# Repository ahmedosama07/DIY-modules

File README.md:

# DIY-modules
 This is the repo where I try to recreate electronic modules at home.

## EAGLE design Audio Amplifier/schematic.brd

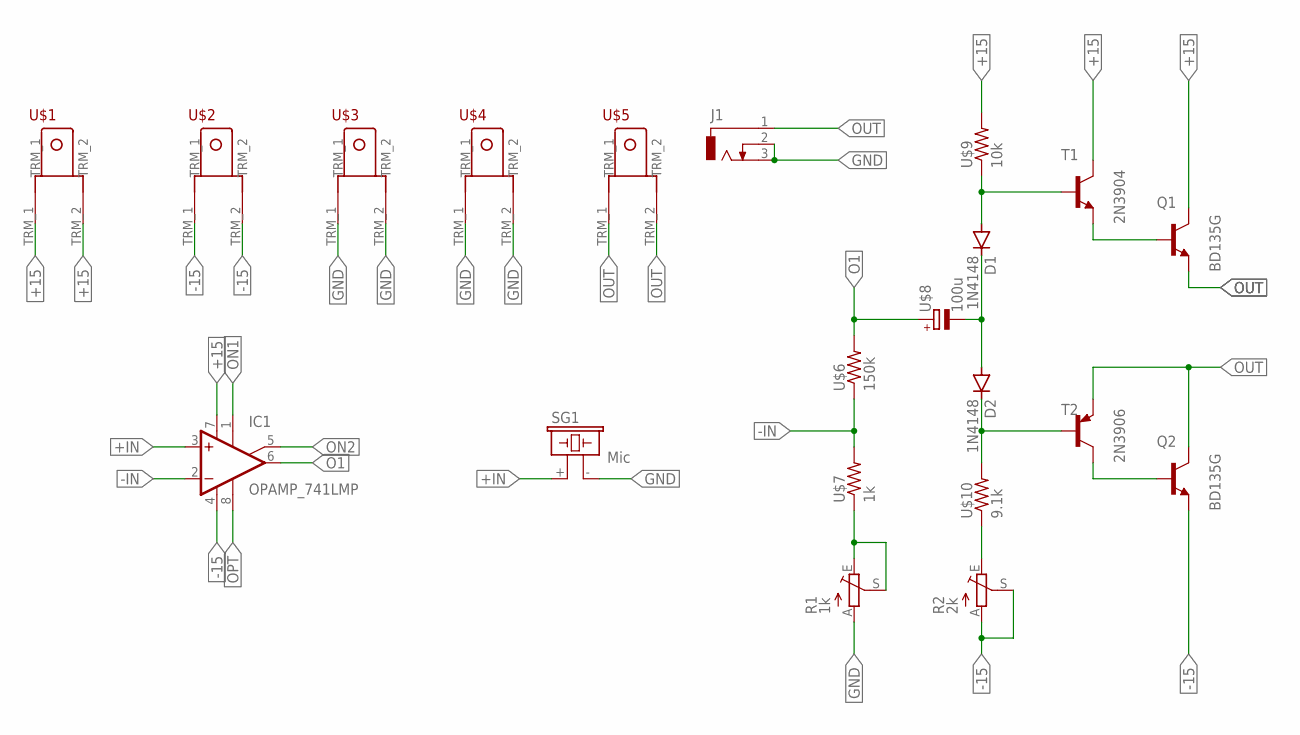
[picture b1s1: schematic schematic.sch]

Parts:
D1, D2: 1N4148; DO35-10
IC1: OPAMP_741LMP; DIL08
J1: CON_JACK; DCJ0303
Q1, Q2: BD135G; TO229P780X300X2000-3
R1: 1k; CA6V
R2: 2k; CA6V
SG1: Mic; F/CM12P
T1: 2N3904; TO92-EBC
T2: 2N3906; TO92-EBC
U$1, U$2, U$3, U$4, U$5: TERMINAL_EDITED
U$6: 150k; 0204/7
U$7: 1k; 0204/7
U$8: 100u; E3,5-8
U$9: 10k; 0204/7
U$10: 9.1k; 0204/7

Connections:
+15: IC1.7 (V+), Q1.2 (C), T1.C, U$1.TRM_1, U$1.TRM_2, U$9.2
+IN: IC1.3 (+IN), SG1.+ (1)
-15: IC1.4 (V-), Q2.1 (E), R2.A, R2.S, U$2.TRM_1, U$2.TRM_2
-IN: IC1.2 (-IN), U$6.1, U$7.2
GND: J1.2, J1.3, R1.A, SG1.- (2), U$3.TRM_1, U$3.TRM_2, U$4.TRM_1, U$4.TRM_2
unnamed: D1.C, D2.A, U$8.-
unnamed: D1.A, T1.B, U$9.1
unnamed: R1.E, R1.S, U$7.1
unnamed: D2.C, T2.B, U$10.2
unnamed: R2.E, U$10.1
unnamed: Q1.3 (B), T1.E
unnamed: Q2.3 (B), T2.C
O1: IC1.6 (OUT), U$6.2, U$8.+
ON1: IC1.1 (ON1)
ON2: IC1.5 (ON2)
OPT: IC1.8 (OPT)
OUT: J1.1, Q1.1 (E), Q2.2 (C), T2.E, U$5.TRM_1, U$5.TRM_2

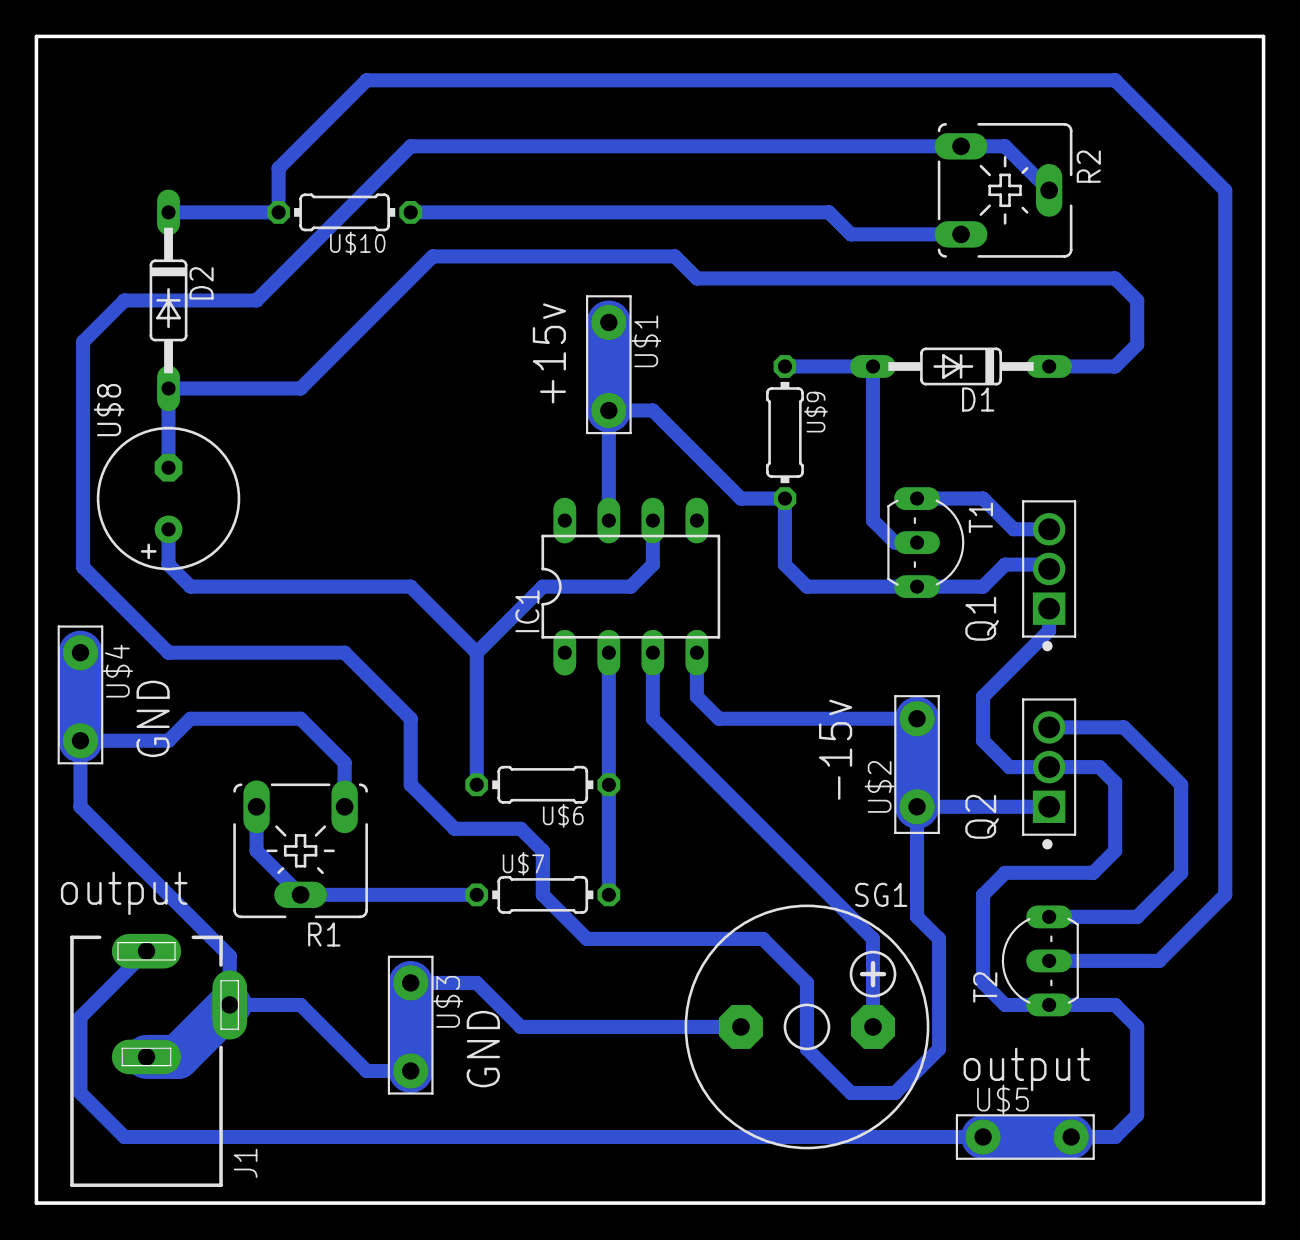
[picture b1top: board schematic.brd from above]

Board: 2 copper layers, 70.8 x 67.3 mm, 21 parts (0 on the bottom side), 14 nets.

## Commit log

2023-04-17 IR sensor module
2023-04-17 Revert "IR sensor module"
2023-04-17 Revert "Merge pull request #2 from ahmedosama07/revert-1-demos"
    This reverts commit cf0b2bfa19d9b68860c3daad4459c7f8ef7cffd9, reversing
    changes made to 7bed61fb79092b1bab31f4d35495a3ab60843b10.
2023-08-21 Audio Amplifier
